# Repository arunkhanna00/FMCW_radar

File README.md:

# FMCW-radar
An FMCW radar PCB. 

Inspired by [Gregory L. Charvat's Coffee Can Radar](https://ocw.mit.edu/resources/res-ll-003-build-a-small-radar-system-capable-of-sensing-range-doppler-and-synthetic-aperture-radar-imaging-january-iap-2011/)

Here is a basic idea of how the radar works:

The schematic and PCB are shown below:

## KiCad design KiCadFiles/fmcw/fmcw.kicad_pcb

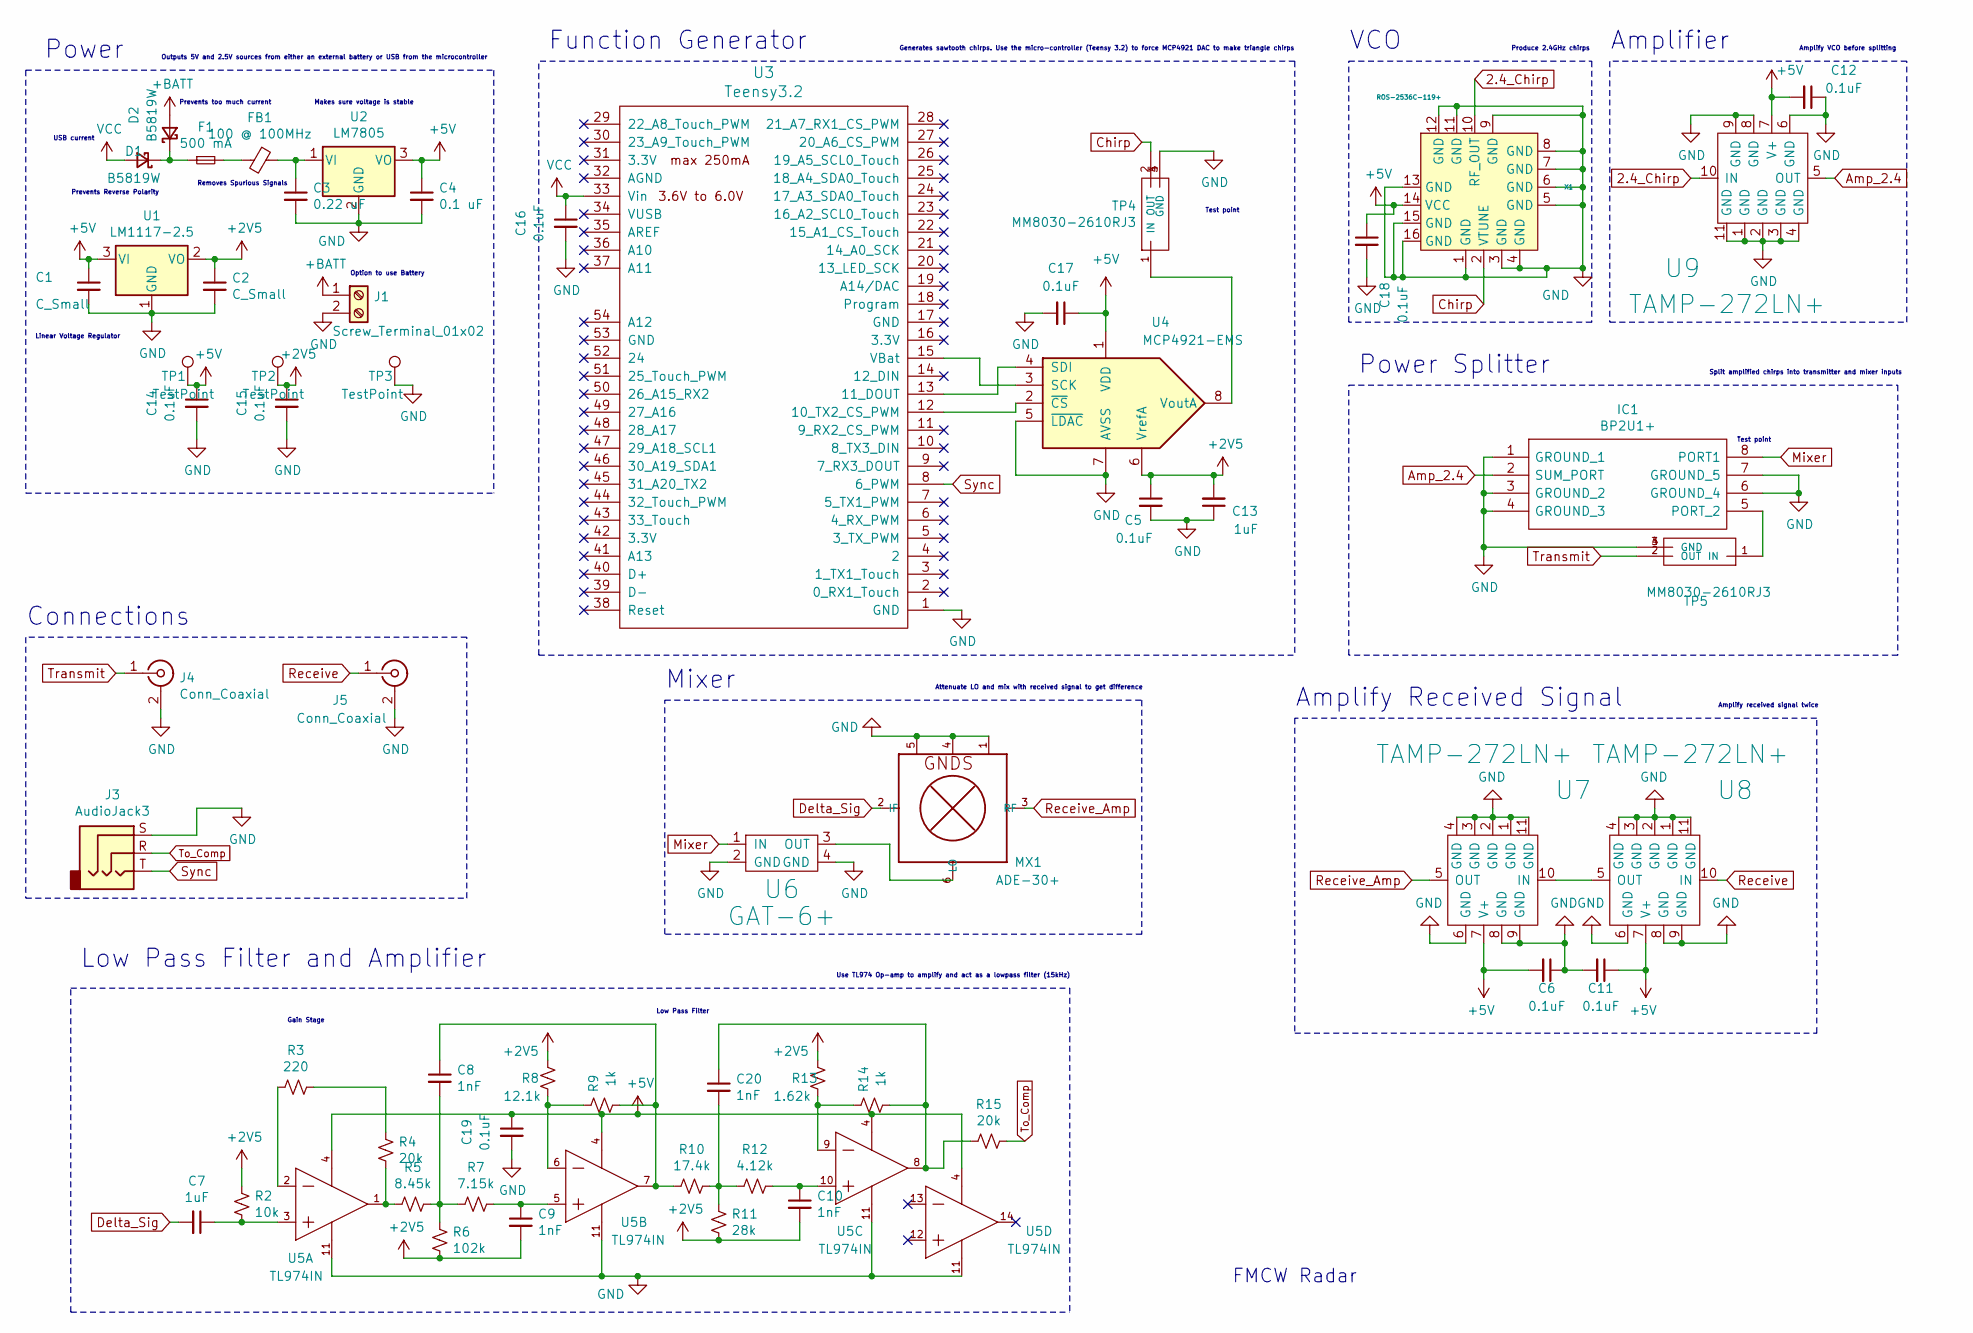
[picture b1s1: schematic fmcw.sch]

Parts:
C1, C2: C_Small; C_0603_1608Metric
C3: 0.22 uF; C_0603_1608Metric
C4: 0.1 uF; C_0603_1608Metric
C5, C6, C11, C12, C14, C15, C16, C17, C18, C19: 0.1uF; C_0603_1608Metric
C7, C13: 1uF; C_0603_1608Metric
C8, C9, C10, C20: 1nF; C_0603_1608Metric
D1, D2: B5819W; D_0603_1608Metric
F1: 500 mA; Fuse_1206_3216Metric
FB1: 100 @ 100MHz
IC1: BP2U1+; SOIC127P597X196-8N; Manufacturer_Part_Number BP2U1+
J1: Screw_Terminal_01x02; TerminalBlock_4Ucon_1x02_P3.50mm_Horizontal
J3: AudioJack3; Jack_3.5mm_CUI_SJ-3523-SMT_Horizontal
J4, J5: Conn_Coaxial; SMA_Amphenol_132289_EdgeMount
MX1: ADE-30+; CD636
R2: 10k; R_0603_1608Metric
R3: 220; R_0603_1608Metric
R4, R15: 20k; R_0603_1608Metric
R5: 8.45k; R_0603_1608Metric
R6: 102k; R_0603_1608Metric
R7: 7.15k; R_0603_1608Metric
R8: 12.1k; R_0603_1608Metric
R9, R14: 1k; R_0603_1608Metric
R10: 17.4k; R_0603_1608Metric
R11: 28k; R_0603_1608Metric
R12: 4.12k; R_0603_1608Metric
R13: 1.62k; R_0603_1608Metric
TP1, TP2, TP3: TestPoint; TestPoint_Pad_1.0x1.0mm
TP4, TP5: MM8030-2610RJ3; MURATA_MM8030-2610RJ3; PARTREV Nov. 1, 2018
U1: LM1117-2.5; SOT-223
U2: LM7805; SOT-223
U3: Teensy3.2; Teensy30_31_32_LC
U4: MCP4921-EMS; MCP4921-E_SN
U5: TL974IN; Texas_Instruments-TL974IN-Manufacturer_Recommended; Rating Catalog
U6: GAT-6+; GAT-3
U7, U8, U9: TAMP-272LN+
X1: ROS-2536C-119+; ROS­2536C­119

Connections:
2.4_Chirp: U9.10 (IN), X1.10 (RF_OUT)
+2V5: C2.1, C5.1, C9.2, C10.2, C13.2, C15.1, R2.1, R6.2, R8.1, R11.2, R13.1, TP2.1, U1.2 (VO), U1.4, U4.6 (VrefA)
+5V: C1.1, C4.1, C6.2, C11.1, C12.2, C14.1, C17.1, C18.1, C19.1, TP1.1, U1.3 (VI), U2.3 (VO), U2.4, U4.1 (VDD), U5.4 (VCC+), U7.7 (V+), U8.7 (V+), U9.7 (V+), X1.14 (VCC)
+BATT: D2.2 (A), J1.1
Amp_2.4: IC1.2 (SUM_PORT), U9.5 (OUT)
Chirp: TP4.2 (OUT), X1.2 (VTUNE)
Delta_Sig: C7.2, MX1.2 (IF)
GND: C1.2, C2.2, C3.2, C4.2, C5.2, C6.1, C11.2, C12.1, C13.1, C14.2, C15.2, C16.2, C17.2, C18.2, C19.2, IC1.1 (GROUND_1), IC1.3 (GROUND_2), IC1.4 (GROUND_3), IC1.6 (GROUND_4), IC1.7 (GROUND_5), J1.2, J3.S, J4.2 (Ext), J5.2 (Ext), MX1.1, MX1.4, MX1.5, TP3.1, TP4.3 (GND), TP4.4 (GND), TP5.3 (GND), TP5.4 (GND), U1.1 (GND), U2.2 (GND), U3.1 (GND), U4.5 (~LDAC~), U4.7 (AVSS), U5.11 (VCC-), U6.2 (GND), U6.4 (GND), U7.1 (GND), U7.2 (GND), U7.3 (GND), U7.4 (GND), U7.6 (GND), U7.8 (GND), U7.9 (GND), U7.11 (GND), U8.1 (GND), U8.2 (GND), U8.3 (GND), U8.4 (GND), U8.6 (GND), U8.8 (GND), U8.9 (GND), U8.11 (GND), U9.1 (GND), U9.2 (GND), U9.3 (GND), U9.4 (GND), U9.6 (GND), U9.8 (GND), U9.9 (GND), U9.11 (GND), X1.1 (GND), X1.3 (GND), X1.4 (GND), X1.5 (GND), X1.6 (GND), X1.7 (GND), X1.8 (GND), X1.9 (GND), X1.11 (GND), X1.12 (GND), X1.13 (GND), X1.15 (GND), X1.16 (GND)
Mixer: IC1.8 (PORT1), U6.1 (IN)
unnamed: C3.1, FB1.1, U2.1 (VI)
unnamed: C7.1, R2.2, U5.3 (IN1+)
unnamed: C8.1, R9.2, R10.2, U5.7 (OUT2)
unnamed: C8.2, R5.1, R6.1, R7.2
unnamed: C9.1, R7.1, U5.5 (IN2+)
unnamed: C10.1, R12.1, U5.10 (IN3+)
unnamed: C20.1, R14.2, R15.1, U5.8 (OUT3)
unnamed: C20.2, R10.1, R11.1, R12.2
unnamed: D1.1 (K), D2.1 (K), F1.1
unnamed: F1.2, FB1.2
unnamed: IC1.5 (PORT_2), TP5.1 (IN)
unnamed: MX1.6 (LO), U6.3 (OUT)
unnamed: R3.1, U5.2 (IN1-)
unnamed: R3.2, R4.1
unnamed: R4.2, R5.2, U5.1 (OUT1)
unnamed: R8.2, R9.1, U5.6 (IN2-)
unnamed: R13.2, R14.1, U5.9 (IN3-)
unnamed: TP4.1 (IN), U4.8 (VoutA)
unnamed: U3.12 (10_TX2_CS_PWM), U4.2 (~CS~)
unnamed: U3.13 (11_DOUT), U4.4 (SDI)
unnamed: U3.15 (VBat), U4.3 (SCK)
unnamed: U7.10 (IN), U8.5 (OUT)
Receive: J5.1 (In), U8.10 (IN)
Receive_Amp: MX1.3 (RF), U7.5 (OUT)
Sync: J3.T, U3.8 (6_PWM)
To_Comp: J3.R, R15.2
Transmit: J4.1 (In), TP5.2 (OUT)
VCC: C16.1, D1.2 (A), U3.33 (Vin)

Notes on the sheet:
Prevents Reverse Polarity
Prevents too much current
Makes sure voltage is stable
USB current
Linear Voltage Regulator
Power
Function Generator
Outputs 5V and 2.5V sources from either an external battery or USB from the microcontroller
Generates sawtooth chirps. Use the micro-controller (Teensy 3.2) to force MCP4921 DAC to make triangle chirps
Test point
Low Pass Filter and Amplifier
Gain Stage
Low Pass Filter
VCO
Produce 2.4GHz chirps
Amplifier
Power Splitter
Split amplified chirps into transmitter and mixer inputs
Amplify VCO before splitting
Use TL974 Op-amp to amplify and act as a lowpass filter (15kHz)
Connections
Mixer
Attenuate LO and mix with received signal to get difference
Amplify Received Signal
Amplify received signal twice
FMCW Radar
Option to use Battery
Removes Spurious Signals

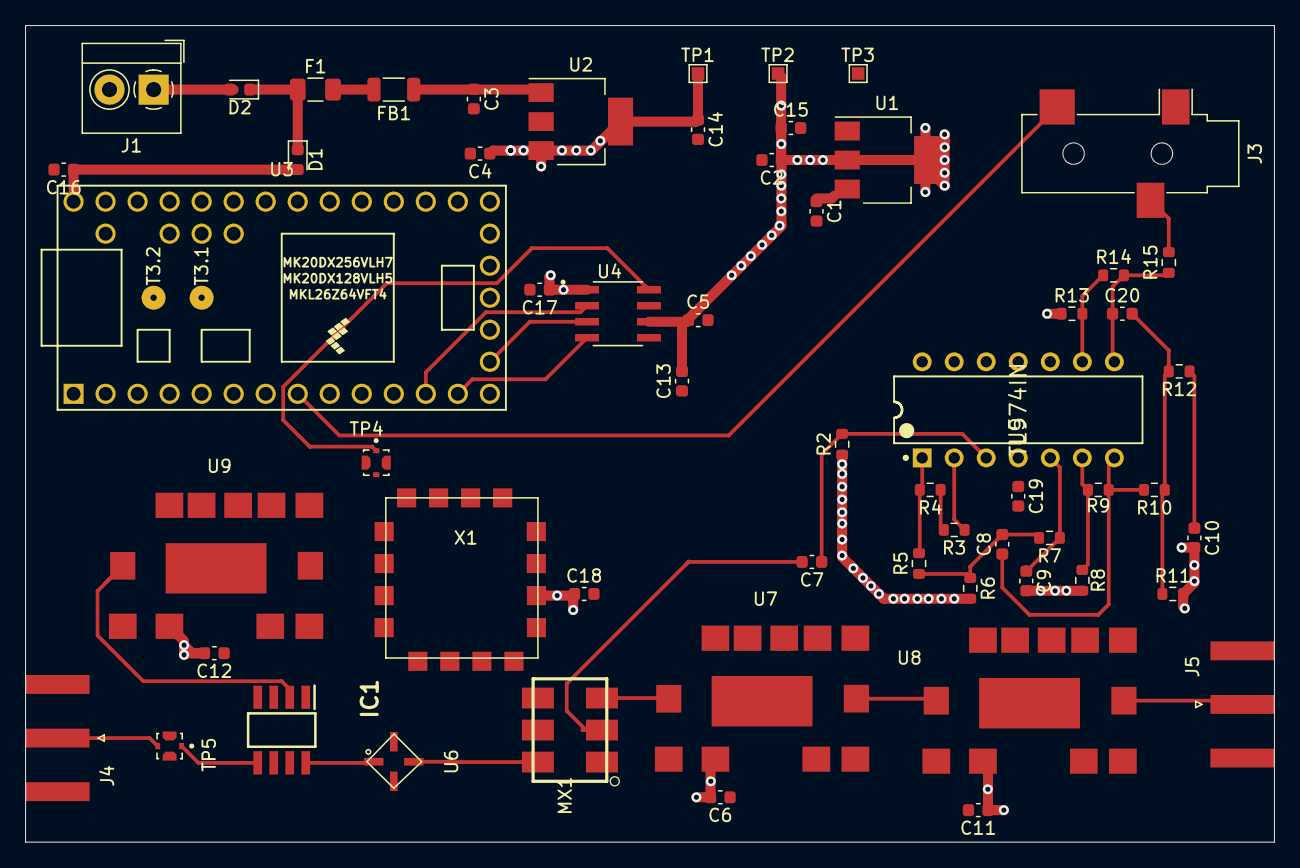
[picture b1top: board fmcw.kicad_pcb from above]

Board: 4 copper layers, 99.1 x 64.8 mm, 59 parts (0 on the bottom side), 37 nets.

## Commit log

2021-08-25 add gerber files
2021-08-25 added code
